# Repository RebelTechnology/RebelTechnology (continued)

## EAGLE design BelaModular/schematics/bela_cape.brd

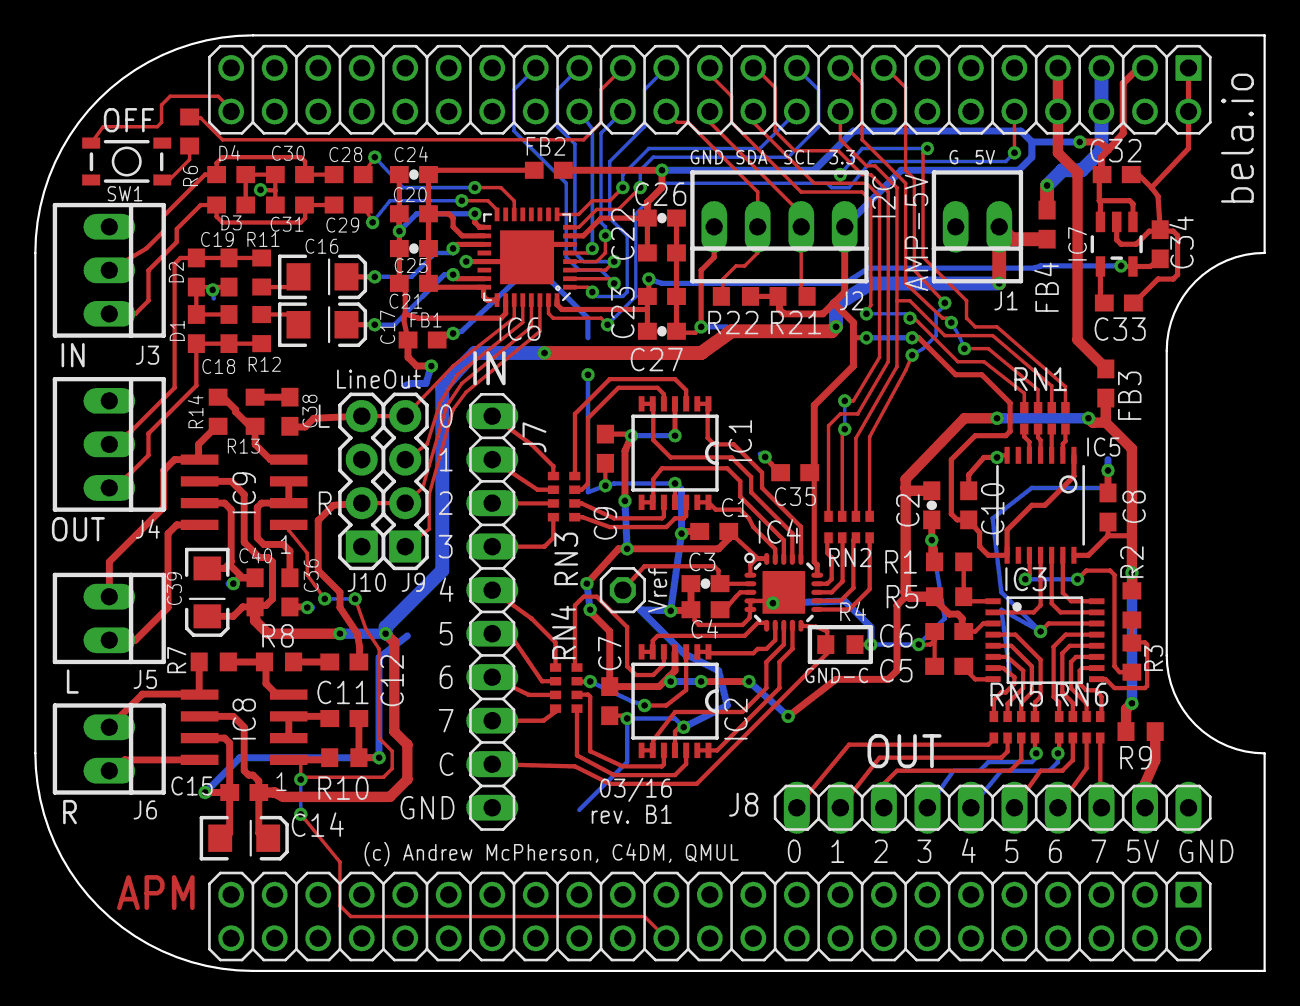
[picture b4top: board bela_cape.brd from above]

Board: 2 copper layers, 71.8 x 54.6 mm, 90 parts (0 on the bottom side), 114 nets.

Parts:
C1, C4, C5, C6, C7, C8, C9, C10, C11, C15, C35, C36, C40: 0.1uF; C0603
C2, C3: 10uF; 0603-CAP
C12, C38: 1uF; C0603
C14, C39: 47uF; EIA3216
C16, C17: 47uf; EIA3216
C18, C19, C30, C31: 47pF; C0603
C20, C21, C22, C23, C28, C29: 0.1uf; C0603
C24, C25, C26, C27: 10uf,10V; 0603-CAP
C32: 1uf; C0603
C33: .01uf; C0603
C34: 2.2uf; C0603
D1, D2, D3, D4: PGB0010603MR; 0603
FB1, FB2, FB3, FB4: FB; 0603
IC1, IC2: ADD8704RU; TSSOP14
IC3: AD5668; TSSOP16-PW
IC4: AD7699; LFCSP20-LEADS
IC5: TSSOP14
IC6: TLV320AIC3104; QFN-32
IC7: V_REG_LDOSMD; SOT23-5
IC8, IC9: LM4876; SO8
J1, J5, J6: 22-23-2021
J2: 22-23-2041
J3, J4: 22-23-2031
J7, J8: 1X10
J9, J10: 1X04
R1, R2, R4, R6: 0; R0603
R3, R5: DNI; R0603
R7, R8, R10, R13, R14: 22k; R0603
R9: 100; R0603
R11, R12: 33; R0603
R21, R22: 2.2k; R0603
RN1, RN2: 22; 0603-ARC
RN3, RN4, RN5, RN6: 220; 0603-ARC
S1: SWITCH-MOMENTARY-2SMD-5; TACTILE_SWITCH_SMD-4
TP1: 1X01
U$1: BEAGLEBONE_OUTLINE; BEAGLEBONE_SHIELD

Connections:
1.8V: C23.1, C27.2, C34.1, IC6.32, IC7.5
3.3V: C10.1, C22.1, C26.2, C32.1, C35.1, FB2.2, IC4.15, IC5.1, IC5.8, IC6.7, IC7.1, IC7.3, J2.1, R21.2, R22.2, U$1.49
+5V_ADC_DAC: C1.1, C2.1, C6.1, C7.1, C8.1, C9.1, FB3.1, IC1.4, IC2.4, IC3.3, IC4.1, IC4.20, IC5.14, R2.1, R5.1, R9.2
+5V_AMP: C14.A, C15.1, C39.A, C40.1, FB4.2, IC8.6, IC9.6, J1.1
+5V_POW: FB4.1, U$1.51, U$1.52
+5V_SYS: FB3.2, U$1.53, U$1.54
AGND: C11.2, C14.C, C15.2, C18.2, C19.2, C20.2, C21.2, C24.1, C25.1, C30.2, C31.1, C36.2, C39.C, C40.2, D1.1, D2.1, D3.1, D4.1, FB1.1, IC6.17, IC6.26, IC8.7, IC9.7, J3.1, J4.1, R10.2
AMP_SH/: IC8.1, IC9.1, R10.1, U$1.26
AUDIO_INL: C28.1, C30.1, D4.2, J3.2
AUDIO_INR: C29.2, C31.2, D3.2, J3.3
AUD_3V3: C20.1, C21.1, C24.2, C25.2, FB2.1, IC6.18, IC6.24, IC6.25
AUD_BCLK: IC6.2, U$1.77
AUD_DIN: IC6.5, U$1.76
AUD_DOUT: IC6.4, U$1.74
AUD_HPLOUT: C16.A, IC6.19
AUD_HPROUT: C17.A, IC6.23
AUD_MCLK: IC6.1, U$1.71
AUD_WCLK: IC6.3, U$1.75
DGND: C1.2, C2.2, C3.2, C4.2, C5.2, C6.2, C7.2, C8.2, C9.2, C10.2, C22.2, C23.2, C26.1, C27.1, C32.2, C33.2, C34.2, C35.2, FB1.2, IC1.11, IC2.11, IC3.14, IC4.4, IC4.5, IC4.EXP, IC5.7, IC6.6, IC6.21, IC6.EP, IC7.2, J1.2, J2.4, J7.10, J8.10, R1.2, R4.1, S1.4, U$1.1, U$1.2, U$1.47, U$1.48, U$1.89, U$1.90, U$1.91, U$1.92
HPL: C19.1, D2.2, J4.2, R11.1
HPR: C18.1, D1.2, J4.3, R12.1
I2C1_SCL: J2.2, R21.1, U$1.70
I2C1_SDA: J2.3, R22.1, U$1.72
LEFT_LOM: IC6.28, J9.3
LEFT_LOP: IC6.27, J9.4
LEFT_LOP_RETURN: C38.2, J10.4
LINE1LP: C28.2, IC6.14
LINE1RP: C29.1, IC6.16
unnamed: IC3.16, IC5.13
unnamed: IC3.15, IC5.12
unnamed: IC3.2, IC5.11
unnamed: IC3.9, R2.2, R3.2
unnamed: IC1.1, IC1.2, IC4.16
unnamed: IC1.6, IC1.7, IC4.17
unnamed: IC1.8, IC1.9, IC4.18
unnamed: IC1.13, IC1.14, IC4.19
unnamed: IC2.1, IC2.2, IC4.7
unnamed: IC2.6, IC2.7, IC4.6
unnamed: IC2.8, IC2.9, IC4.8
unnamed: IC2.13, IC2.14, IC4.9
unnamed: IC5.10, R3.1
unnamed: IC4.11, RN2.4
unnamed: C5.1, IC3.8
unnamed: IC5.2, RN1.8
unnamed: IC5.3, RN1.7
unnamed: IC5.4, RN1.6
unnamed: IC5.5, RN1.5
unnamed: IC4.12, RN2.3
unnamed: C3.1, IC4.2, TP1.1
unnamed: C4.1, IC4.3
unnamed: IC4.13, RN2.2
unnamed: IC4.14, RN2.1
unnamed: IC4.10, J7.9, R4.2
unnamed: IC9.4, R13.1, R14.2
unnamed: IC1.3, RN3.4
unnamed: IC8.4, R7.2, R8.1
unnamed: IC1.5, RN3.3
unnamed: IC1.10, RN3.2
unnamed: IC1.12, RN3.1
unnamed: IC2.5, RN4.4
unnamed: IC2.3, RN4.3
unnamed: IC2.10, RN4.2
unnamed: IC2.12, RN4.1
unnamed: IC3.1, R1.1, R5.2
unnamed: J7.1, RN3.5
unnamed: J7.2, RN3.6
unnamed: J7.3, RN3.7
unnamed: J7.4, RN3.8
unnamed: J7.5, RN4.5
unnamed: J7.6, RN4.6
unnamed: J7.7, RN4.7
unnamed: J7.8, RN4.8
unnamed: IC3.7, RN5.4
unnamed: IC3.6, RN5.3
unnamed: IC3.5, RN5.2
unnamed: IC3.4, RN5.1
unnamed: IC3.13, RN6.4
unnamed: IC3.12, RN6.3
unnamed: IC3.11, RN6.2
unnamed: J8.8, RN6.8
unnamed: C11.1, IC8.2, IC8.3
unnamed: C16.C, R11.2
unnamed: C12.2, R8.2
unnamed: IC8.5, J6.1, R7.1
unnamed: R6.1, S1.1
unnamed: C17.C, R12.2
unnamed: C36.1, IC9.2, IC9.3
unnamed: J8.9, R9.1
unnamed: C33.1, IC7.4
unnamed: C38.1, R13.2
unnamed: IC9.5, J5.1, R14.1
unnamed: IC9.8, J5.2
unnamed: IC8.8, J6.2
unnamed: IC3.10, RN6.1
unnamed: J8.7, RN6.7
unnamed: J8.6, RN6.6
unnamed: J8.5, RN6.5
unnamed: J8.4, RN5.8
unnamed: J8.3, RN5.7
unnamed: J8.2, RN5.6
unnamed: J8.1, RN5.5
RESETN: IC6.31, U$1.56
RIGHT_LOP: IC6.29, J9.2
RIGHT_LOP_RETURN: C12.1, J10.2
RIGHT_ROM: IC6.30, J9.1
SCL: IC6.8, U$1.65
SDA: IC6.9, U$1.66
SHUTDOWN_REQ/: R6.2, U$1.73
SPI_ADC_CNV: RN2.5, U$1.61
SPI_DAC_CLR/: RN1.4, U$1.69
SPI_DAC_SYNC/: RN1.3, U$1.63
SPI_MISO: RN2.8, U$1.67
SPI_MOSI: RN1.2, RN2.6, U$1.64
SPI_SCK: RN1.1, RN2.7, U$1.68

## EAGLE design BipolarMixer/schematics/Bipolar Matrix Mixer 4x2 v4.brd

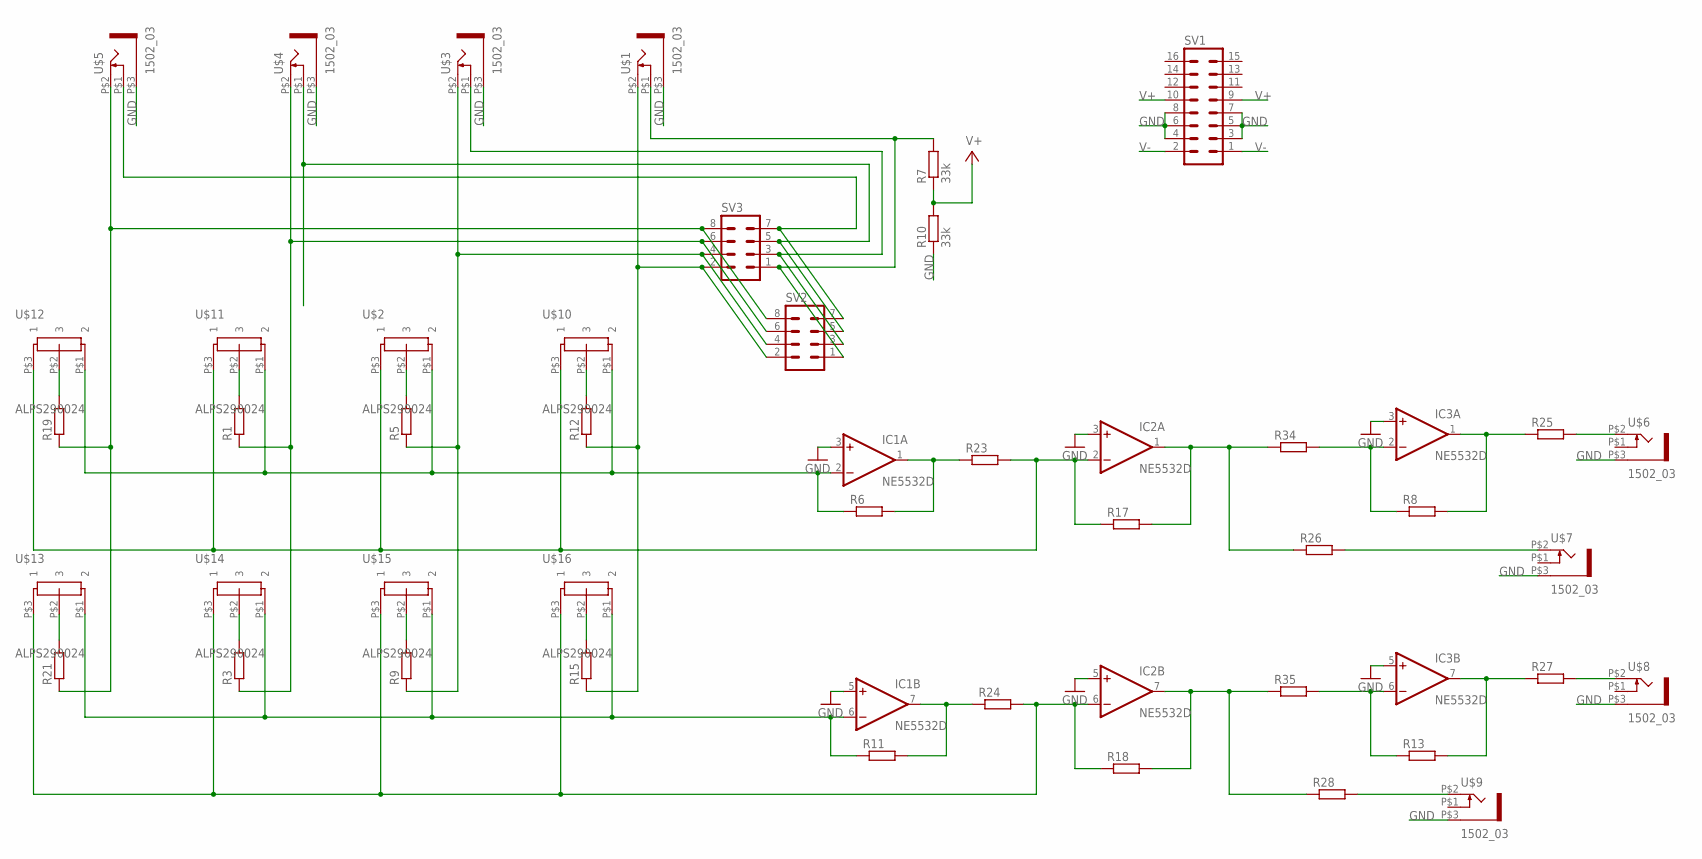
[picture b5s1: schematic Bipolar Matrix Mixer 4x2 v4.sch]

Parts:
IC1, IC2, IC3: NE5532D; SO08
R1, R3, R5, R6, R8, R9, R11, R12, R13, R15, R17, R18, R19, R21, R23, R24, R25, R26, R27, R28, R34, R35: R-EU_R0603; R0603
R7, R10: 33k; R0603
SV1: MA08-2
SV2, SV3: MA04-2
U$1, U$3, U$4, U$5, U$6, U$7, U$8, U$9: 1502_03
U$2, U$10, U$11, U$12, U$13, U$14, U$15, U$16: ALPS290024; POT

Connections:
GND: IC1.3 (+IN), IC1.5 (+IN), IC2.3 (+IN), IC2.5 (+IN), IC3.3 (+IN), IC3.5 (+IN), R10.1, SV1.3, SV1.4, SV1.5, SV1.6, SV1.7, SV1.8, U$1.P$3 (5), U$3.P$3 (5), U$4.P$3 (5), U$5.P$3 (5), U$6.P$3 (5), U$7.P$3 (5), U$8.P$3 (5), U$9.P$3 (5)
unnamed: IC2.1 (OUT), R17.2, R26.1, R34.1
unnamed: R1.1, R3.1, SV2.6, SV3.6, U$4.P$2 (3)
unnamed: IC1.7 (OUT), R11.2, R24.1
unnamed: IC1.1 (OUT), R6.2, R23.1
unnamed: IC3.7 (OUT), R13.2, R27.1
unnamed: IC3.1 (OUT), R8.2, R25.1
unnamed: R19.2, U$12.P$2 (3)
unnamed: R21.2, U$13.P$2 (3)
unnamed: R25.2, U$6.P$2 (3)
unnamed: R26.2, U$7.P$2 (3)
unnamed: R1.2, U$11.P$2 (3)
unnamed: R3.2, U$14.P$2 (3)
unnamed: IC2.7 (OUT), R18.2, R28.1, R35.1
unnamed: R27.2, U$8.P$2 (3)
unnamed: IC2.2 (-IN), R17.1, R23.2, U$2.P$3 (1), U$10.P$3 (1), U$11.P$3 (1), U$12.P$3 (1)
unnamed: R28.2, U$9.P$2 (3)
unnamed: IC3.2 (-IN), R8.1, R34.2
unnamed: R5.1, R9.1, SV2.4, SV3.4, U$3.P$2 (3)
unnamed: SV2.3, SV3.3, U$3.P$1 (4)
unnamed: R5.2, U$2.P$2 (3)
unnamed: R9.2, U$15.P$2 (3)
unnamed: IC3.6 (-IN), R13.1, R35.2
unnamed: IC1.2 (-IN), R6.1, U$2.P$1 (2), U$10.P$1 (2), U$11.P$1 (2), U$12.P$1 (2)
unnamed: R12.1, R15.1, SV2.2, SV3.2, U$1.P$2 (3)
unnamed: R19.1, R21.1, SV2.8, SV3.8, U$5.P$2 (3)
unnamed: IC2.6 (-IN), R18.1, R24.2, U$13.P$3 (1), U$14.P$3 (1), U$15.P$3 (1), U$16.P$3 (1)
unnamed: IC1.6 (-IN), R11.1, U$13.P$1 (2), U$14.P$1 (2), U$15.P$1 (2), U$16.P$1 (2)
unnamed: R7.2, SV2.1, SV3.1, U$1.P$1 (4)
unnamed: SV2.5, SV3.5, U$4.P$1 (4)
unnamed: SV2.7, SV3.7, U$5.P$1 (4)
unnamed: R12.2, U$10.P$2 (3)
unnamed: R15.2, U$16.P$2 (3)
V+: IC1.8 (V+), IC2.8 (V+), IC3.8 (V+), R7.1, R10.2, SV1.9, SV1.10
V-: IC1.4 (V-), IC2.4 (V-), IC3.4 (V-), SV1.1, SV1.2

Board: 2 copper layers, 46 parts (0 on the bottom side), 35 nets, no tracks yet.

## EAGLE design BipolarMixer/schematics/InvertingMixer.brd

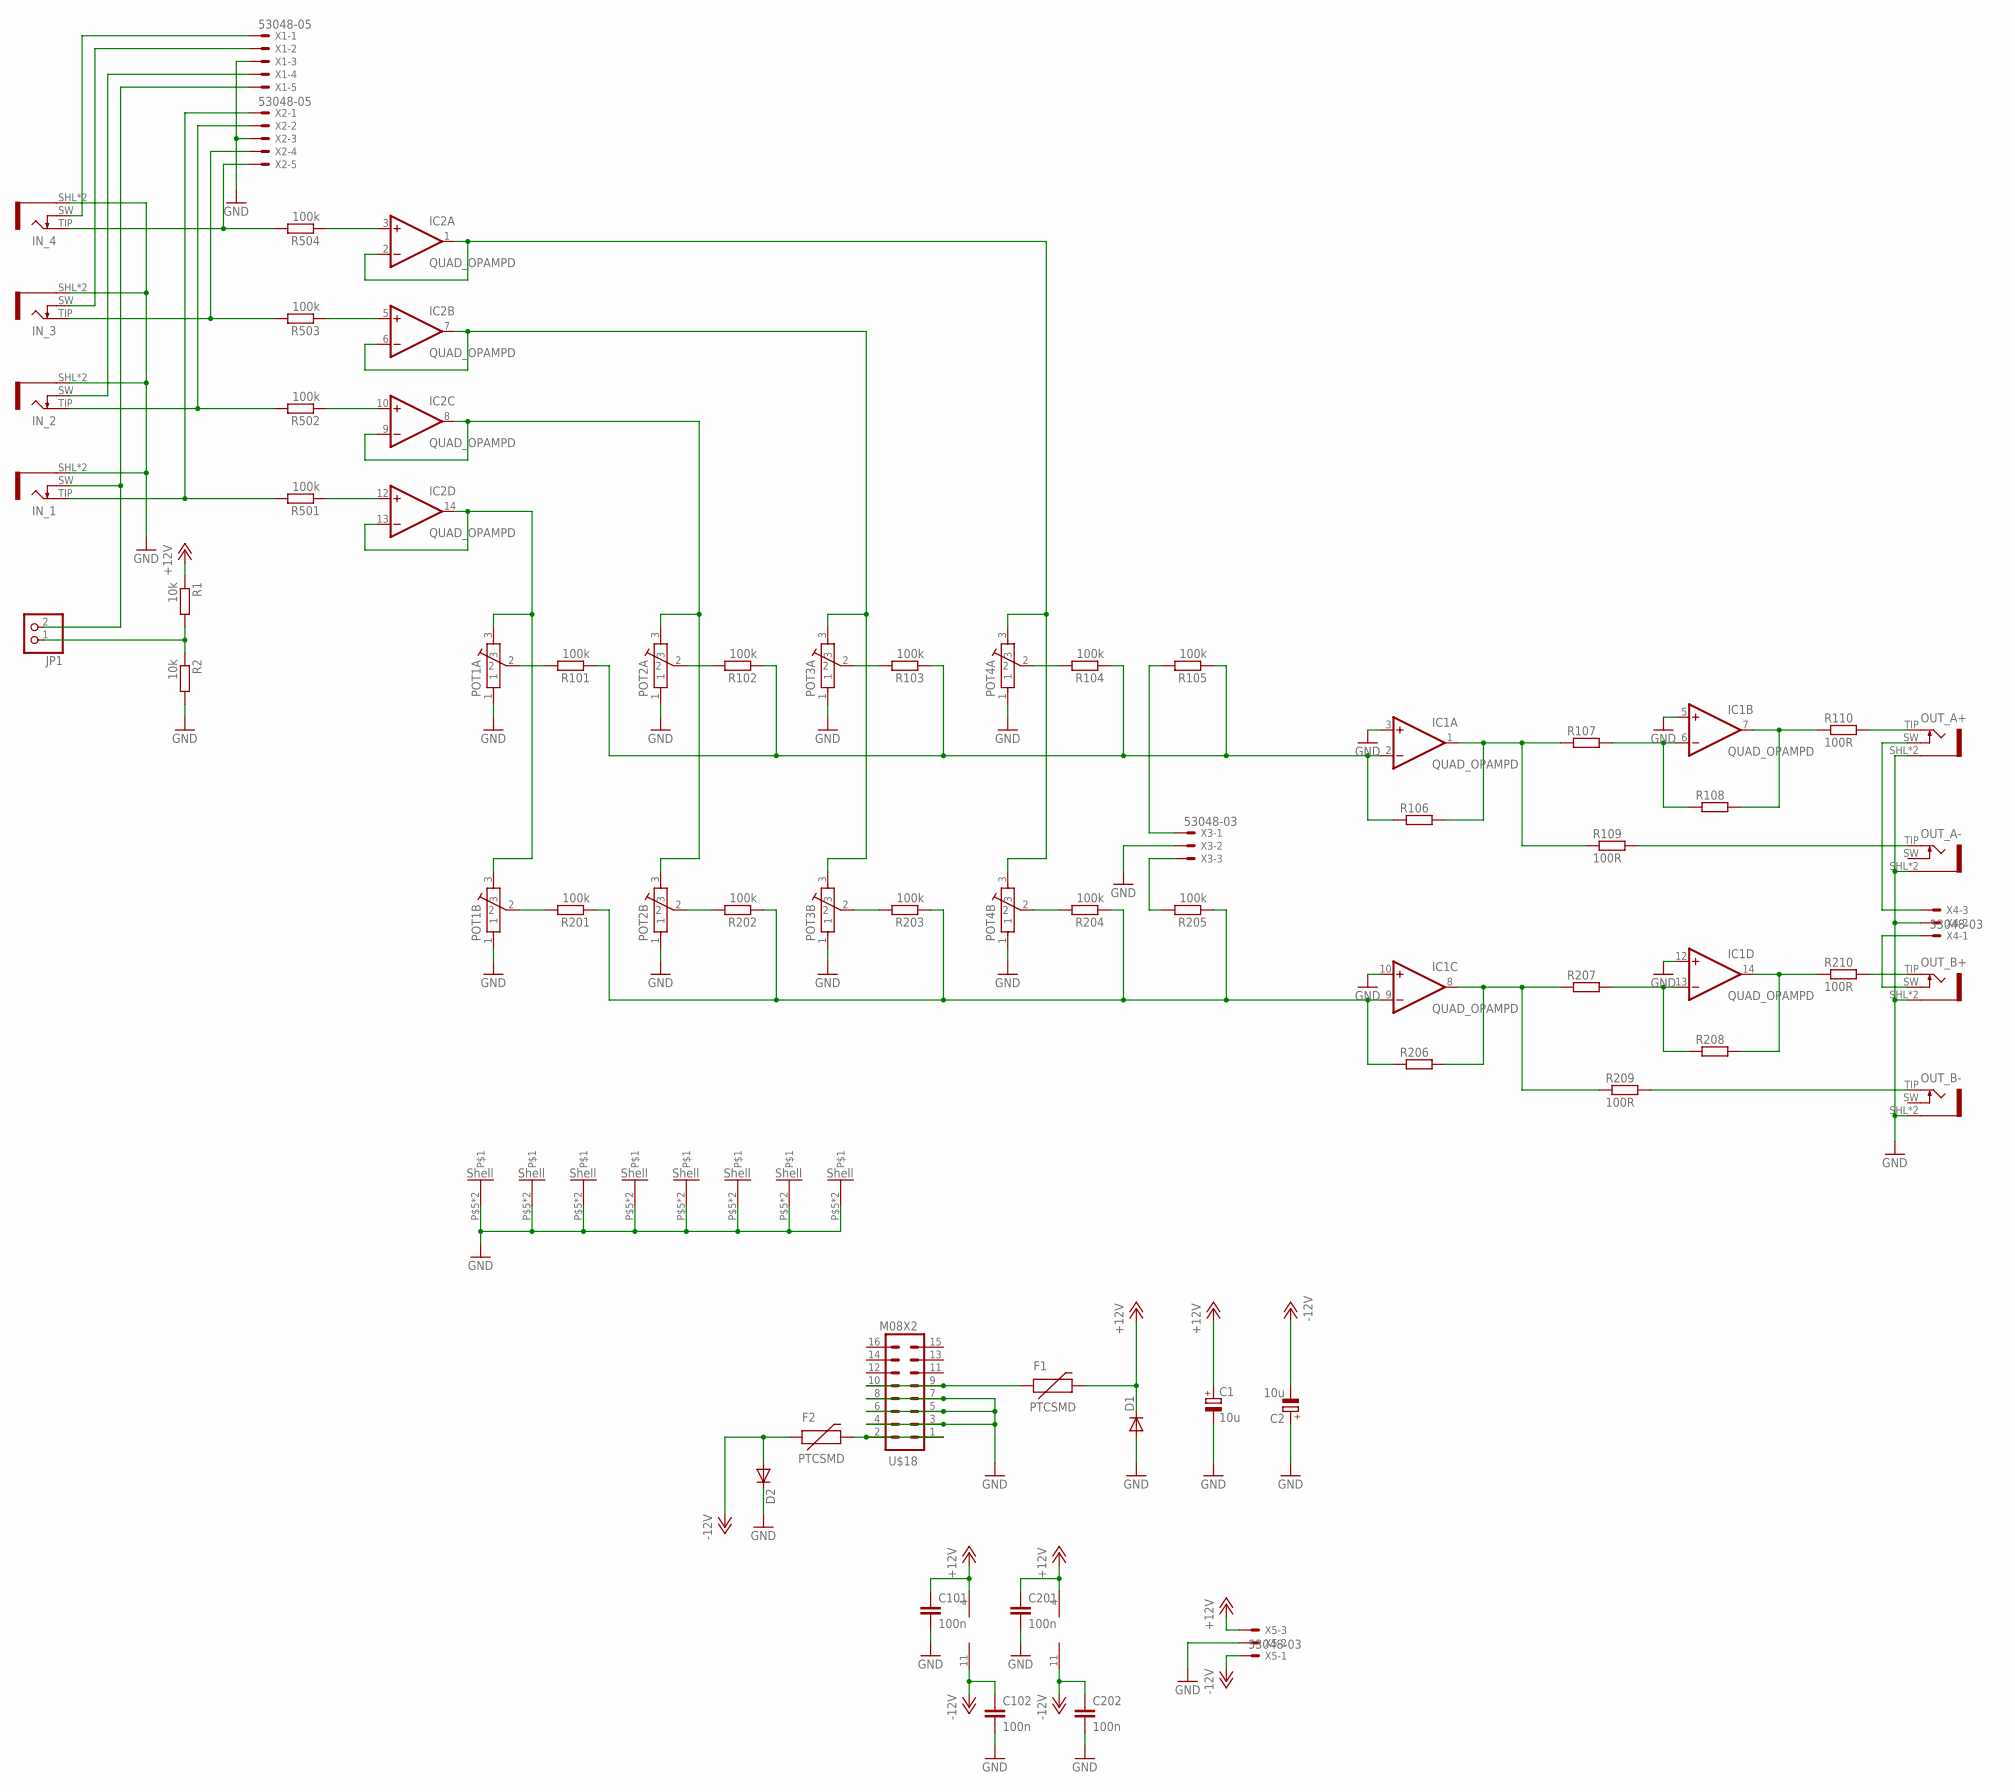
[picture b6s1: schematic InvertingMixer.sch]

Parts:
C1, C2: 10u; PANASONIC_A
C101, C102, C201, C202: 100n; C0603
D1, D2: DIODESMA; SMA-DIODE
F1, F2: PTCSMD; PTC-1206
IC1, IC2: QUAD_OPAMPD; SO14
IN_1, IN_2, IN_3, IN_4: JACK-PJ-301B; PJ-301B
JP1: PINHD-1X2; 1X02
OUT_A+: JACK-PJ-301B; PJ-301B
OUT_A-: JACK-PJ-301B; PJ-301B
OUT_B+: JACK-PJ-301B; PJ-301B
OUT_B-: JACK-PJ-301B; PJ-301B
POT1A, POT1B, POT2A, POT2B, POT3A, POT3B, POT4A, POT4B: POT-ALPS-RK09L1140
R1, R2: 10k; R0603
R101, R102, R103, R104, R105, R201, R202, R203, R204, R205, R501, R502, R503, R504: 100k; R0603
R106, R107, R108, R206, R207, R208: R-EU_R0603; R0603
R109, R110, R209, R210: 100R; R0603
U$18: M08X2; 2X8
X1, X2: 53048-05
X3, X4, X5: 53048-03

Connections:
+12V: C1.+, C101.1, C201.1, D1.C, F1.2, IC1.4 (V+), IC2.4 (V+), R1.1, X5.3
-12V: C2.-, C102.1, C202.1, D2.A, F2.1, IC1.11 (V-), IC2.11 (V-), X5.1
GND: C1.-, C2.+, C101.2, C102.2, C201.2, C202.2, D1.A, D2.C, IC1.3 (+IN), IC1.5 (+IN), IC1.10 (+IN), IC1.12 (+IN), IN_1.SHL (SLEEVE), IN_1.SLV (SLEEVE), IN_2.SHL (SLEEVE), IN_2.SLV (SLEEVE), IN_3.SHL (SLEEVE), IN_3.SLV (SLEEVE), IN_4.SHL (SLEEVE), IN_4.SLV (SLEEVE), OUT_A+.SHL (SLEEVE), OUT_A+.SLV (SLEEVE), OUT_A-.SHL (SLEEVE), OUT_A-.SLV (SLEEVE), OUT_B+.SHL (SLEEVE), OUT_B+.SLV (SLEEVE), OUT_B-.SHL (SLEEVE), OUT_B-.SLV (SLEEVE), POT1A.1, POT1A.P$5, POT1A.P$6, POT1B.1, POT1B.P$5, POT1B.P$6, POT2A.1, POT2A.P$5, POT2A.P$6, POT2B.1, POT2B.P$5, POT2B.P$6, POT3A.1, POT3A.P$5, POT3A.P$6, POT3B.1, POT3B.P$5, POT3B.P$6, POT4A.1, POT4A.P$5, POT4A.P$6, POT4B.1, POT4B.P$5, POT4B.P$6, R2.2, U$18.3, U$18.4, U$18.5, U$18.6, U$18.7, U$18.8, X1.3, X2.3, X3.2, X4.2, X5.2
unnamed: IC1.1 (OUT), R106.2, R107.1, R109.1
unnamed: R205.2, X3.3
unnamed: OUT_A+.SW, X4.3
unnamed: OUT_B+.SW, X4.1
unnamed: IC1.14 (OUT), R208.2, R210.1
unnamed: IC1.7 (OUT), R108.2, R110.1
unnamed: JP1.1, R1.2, R2.1
unnamed: OUT_A+.TIP, R110.2
unnamed: OUT_A-.TIP, R109.2
unnamed: IC1.8 (OUT), R206.2, R207.1, R209.1
unnamed: OUT_B+.TIP, R210.2
unnamed: OUT_B-.TIP, R209.2
unnamed: IC1.6 (-IN), R107.2, R108.1
unnamed: POT1B.2, R201.2
unnamed: IC1.13 (-IN), R207.2, R208.1
unnamed: IC2.8 (OUT), IC2.9 (-IN), POT2A.3, POT2B.3
unnamed: POT1A.2, R101.2
unnamed: POT2B.2, R202.2
unnamed: POT3B.2, R203.2
unnamed: IN_1.TIP, R501.2, X2.1
unnamed: IC2.13 (-IN), IC2.14 (OUT), POT1A.3, POT1B.3
unnamed: IN_4.TIP, R504.2, X2.5
unnamed: IN_3.TIP, R503.2, X2.4
unnamed: IN_2.TIP, R502.2, X2.2
unnamed: IN_4.SW, X1.1
unnamed: IN_3.SW, X1.2
unnamed: IN_2.SW, X1.4
unnamed: IN_1.SW, JP1.2, X1.5
unnamed: IC2.3 (+IN), R504.1
unnamed: IC2.5 (+IN), R503.1
unnamed: POT4B.2, R204.2
unnamed: POT4A.2, R104.2
unnamed: IC2.10 (+IN), R502.1
unnamed: POT3A.2, R103.2
unnamed: IC2.12 (+IN), R501.1
unnamed: POT2A.2, R102.2
unnamed: IC1.2 (-IN), R101.1, R102.1, R103.1, R104.1, R105.1, R106.1
unnamed: IC2.6 (-IN), IC2.7 (OUT), POT3A.3, POT3B.3
unnamed: F1.1, U$18.9, U$18.10
unnamed: F2.2, U$18.1, U$18.2
unnamed: IC2.1 (OUT), IC2.2 (-IN), POT4A.3, POT4B.3
unnamed: IC1.9 (-IN), R201.1, R202.1, R203.1, R204.1, R205.1, R206.1
unnamed: R105.2, X3.1

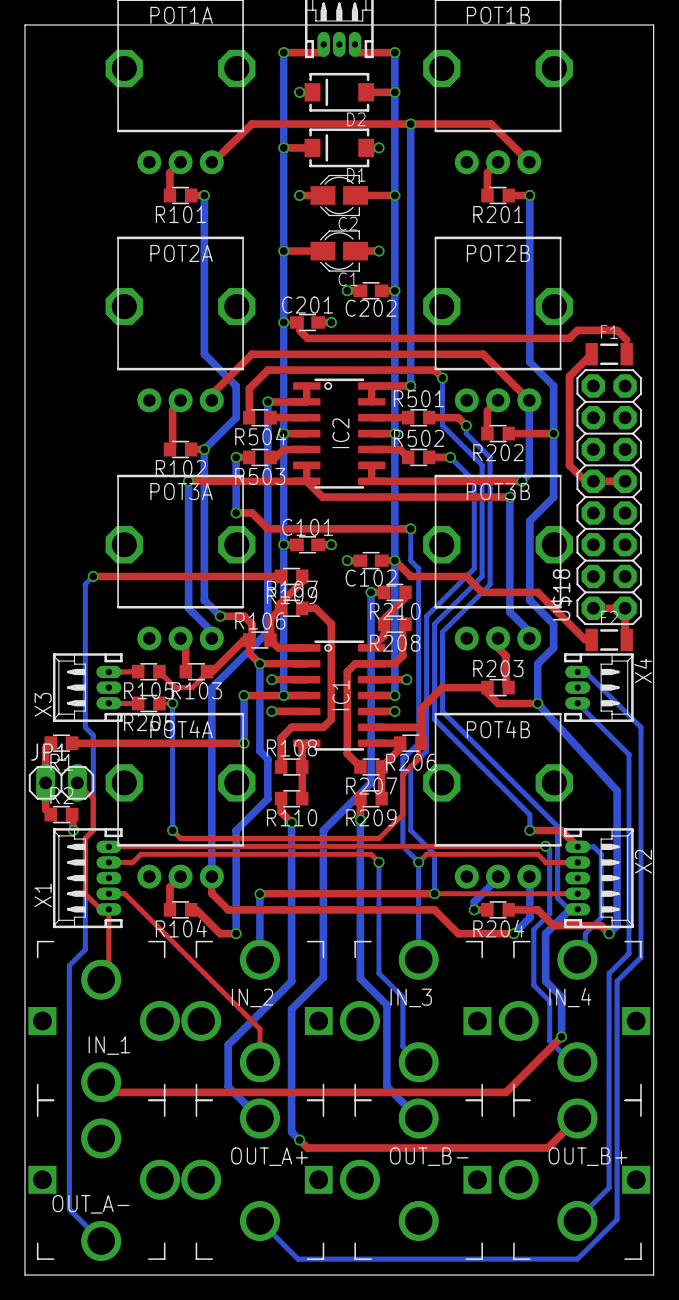
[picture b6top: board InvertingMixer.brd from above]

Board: 2 copper layers, 50.3 x 100.0 mm, 61 parts (0 on the bottom side), 46 nets.

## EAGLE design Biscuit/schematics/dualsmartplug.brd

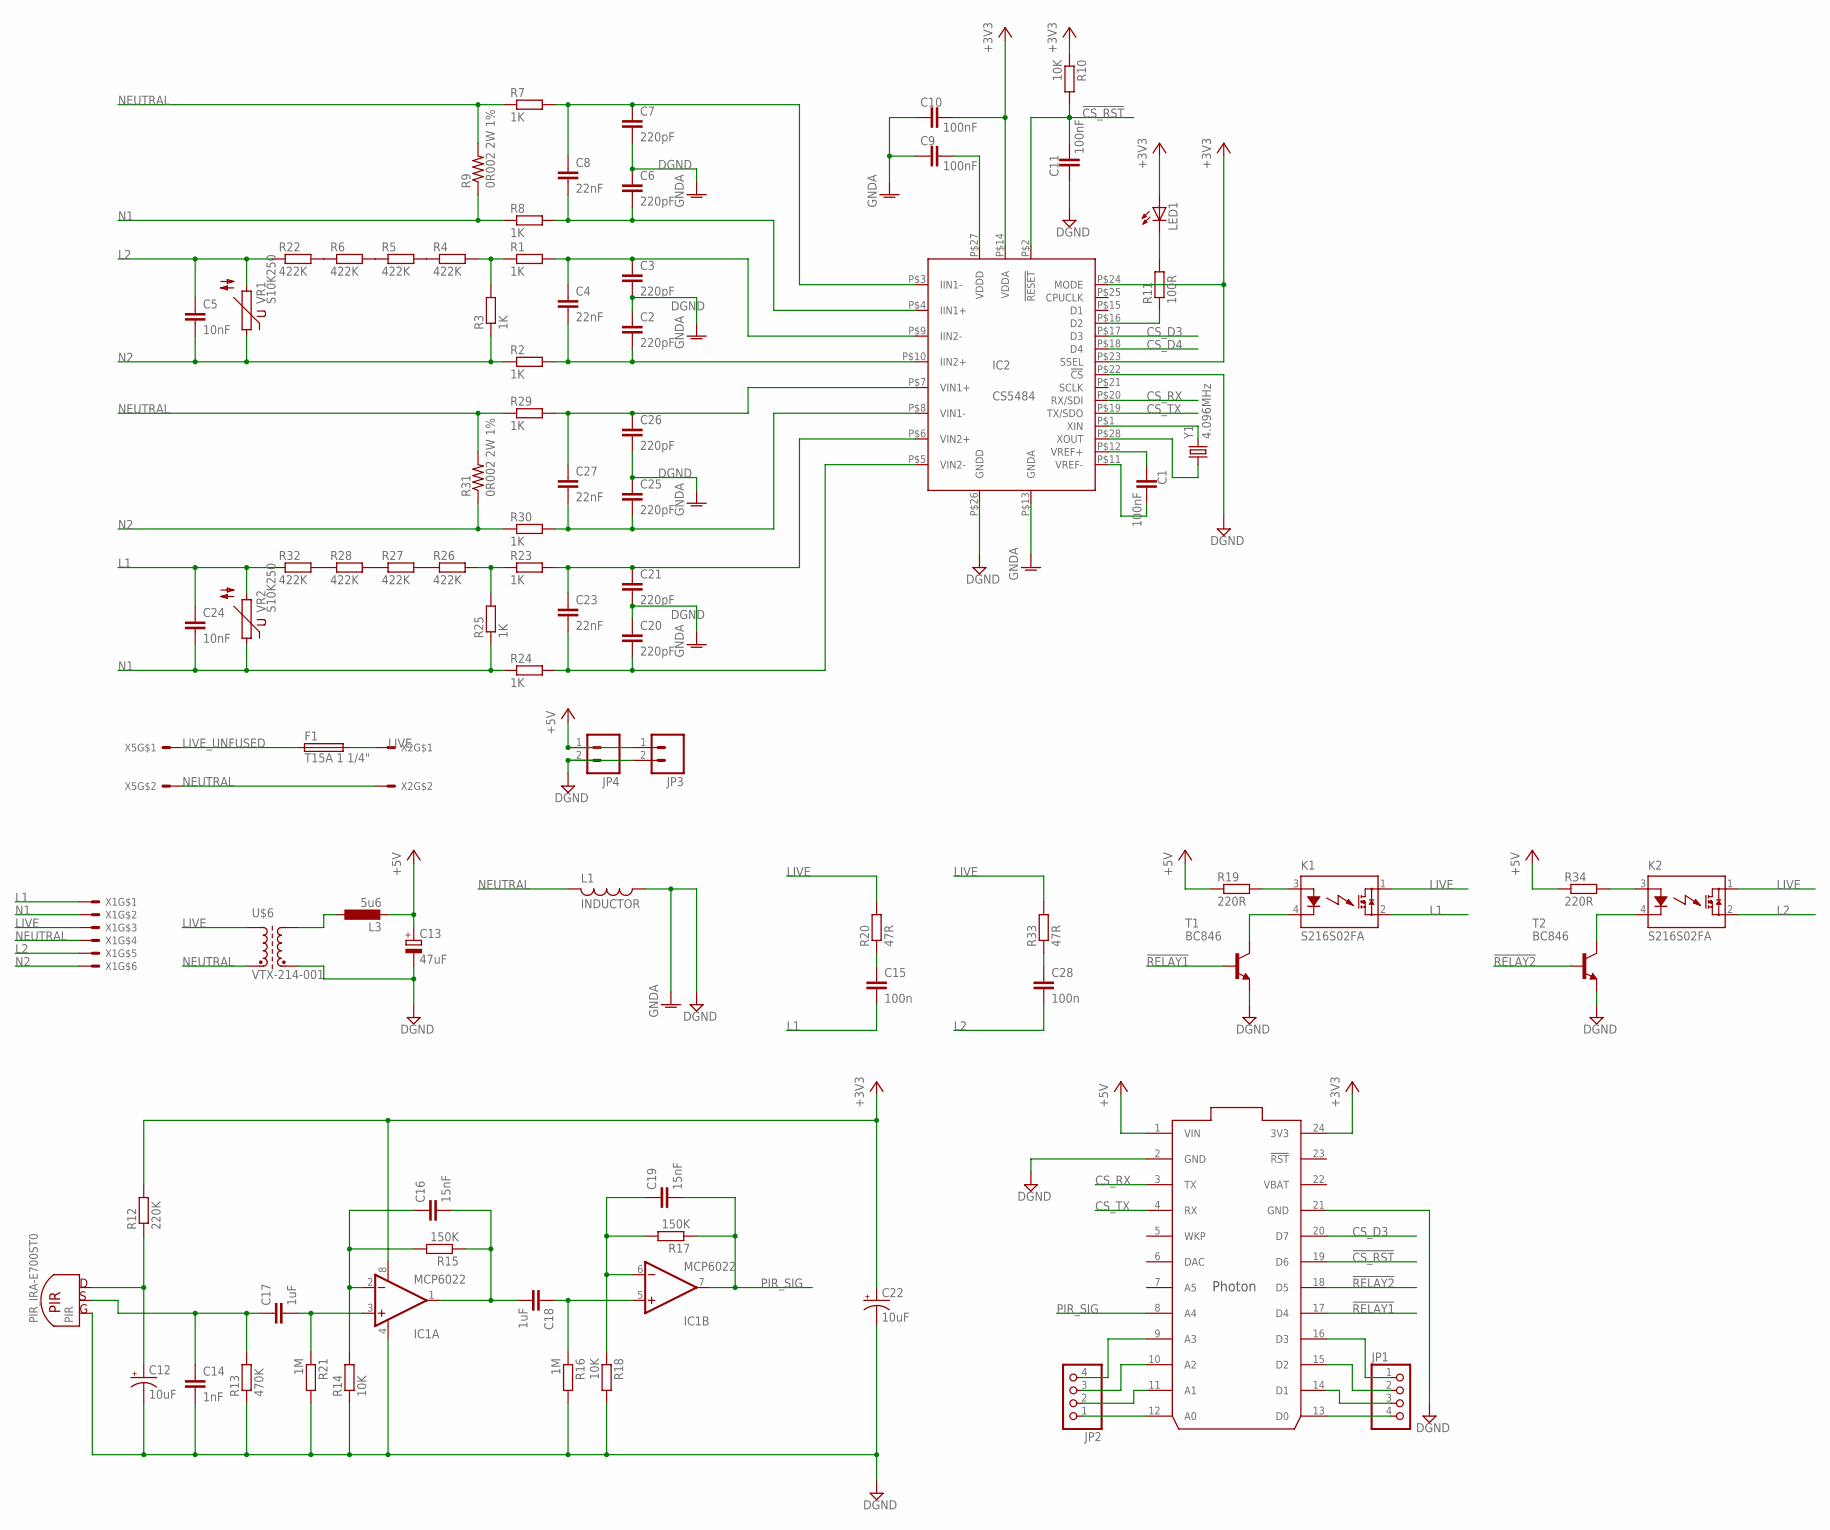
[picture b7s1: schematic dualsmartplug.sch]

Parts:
C1, C9, C10, C11: 100nF; 0603-CAP
C2, C3, C6, C7, C20, C21, C25, C26: 220pF; 0603-CAP
C4, C8, C23, C27: 22nF; 0603-CAP
C5, C24: 10nF; 0603-CAP
C12, C22: 10uF; EIA3216
C13: 47uF; 153CLV-0505
C14: 1nF; 0603-CAP
C15, C28: 100n; C150-054X183
C16, C19: 15nF; 0603-CAP
C17, C18: 1uF; 0603-CAP
F1: T15A 1 1/4"; SHURTER
IC1: MCP6022; SO08
IC2: CS5484; QFN28-5X5
JP1, JP2: PINHD-1X4; 1X04
JP3, JP4: M02PTH; 1X02
K1, K2: S216S02FA; S216S02F
L1: INDUCTOR; 0603
L3: 5u6; ELLCTP
LED1: LEDCHIPLED_1206; CHIPLED_1206
PIR: PIR_IRA-E700ST0
R1, R2, R3, R7, R8, R23, R24, R25, R29, R30: 1K; 0603
R4, R5, R6, R22, R26, R27, R28, R32: 422K; 0603
R9, R31: 0R002 2W 1%; R2512
R10, R14, R18: 10K; 0603
R11: 100R; 0603
R12: 220K; 0603
R13: 470K; 0603
R15, R17: 150K; 0603
R16, R21: 1M; 0603
R19, R34: 220R; 0603
R20, R33: 47R; 0617V
T1, T2: BC846; SOT23
U$2: PHOTON_WITH_HEADERS; PHOTON
U$6: VTX-214-001
VR1, VR2: S10K250
X1: MOLEX-39357-6
X2, X5: MOLEX-39357-2; MOLEX-39357
Y1: 4.096MHz; CRYSTAL-SMD-10.5X4.8-2PIN

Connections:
!CS_RST: C11.2, IC2.P$2 (!RESET), R10.2, U$2.19 (D6)
!RELAY1: T1.1 (B), U$2.17 (D4)
!RELAY2: T2.1 (B), U$2.18 (D5)
+3V3: C10.2, C22.A (+), IC1.8 (V+), IC2.P$14 (VDDA), IC2.P$23 (SSEL), IC2.P$24 (MODE), LED1.A, R10.1, R12.2, U$2.24 (3V3)
+5V: C13.+, JP3.1, JP4.1, L3.2, R19.1, R34.1, U$2.1 (VIN)
CS_D3: IC2.P$17 (D3), U$2.20 (D7)
CS_D4: IC2.P$18 (D4)
CS_RX: IC2.P$20 (RX/SDI), U$2.3 (TX)
CS_TX: IC2.P$19 (TX/SDO), U$2.4 (RX)
DGND: C2.1, C3.2, C6.1, C7.2, C9.1, C10.1, C11.1, C12.C (-), C13.-, C14.2, C20.1, C21.2, C22.C (-), C25.1, C26.2, IC1.4 (V-), IC2.P$13 (GNDA), IC2.P$22 (!CS), IC2.P$26 (GNDD), JP3.2, JP4.2, L1.1, PIR.GND, R13.1, R14.1, R16.2, R18.2, R21.2, T1.2 (E), T2.2 (E), U$2.2 (GND), U$2.21 (GND), U$6.P$V- (E2)
L1: C15.2, C24.1, K1.2 (DS2), R32.1, VR2.2, X1.P$1
L2: C5.1, C28.2, K2.2 (DS2), R22.1, VR1.2, X1.P$5
LIVE: F1.P$7 (2A), K1.1 (DS1), K2.1 (DS1), R20.2, R33.2, U$6.P$L (A1), X1.P$3, X2.P$1
LIVE_UNFUSED: F1.P$5 (1A), X5.P$1
N1: C24.2, R8.1, R9.1, R24.1, R25.1, VR2.1, X1.P$2
N2: C5.2, R2.1, R3.1, R30.1, R31.1, VR1.1, X1.P$6
unnamed: IC2.P$1 (XIN), Y1.P$2 (2)
unnamed: IC2.P$28 (XOUT), Y1.P$1 (1)
unnamed: C1.1, IC2.P$12 (VREF+)
unnamed: C1.2, IC2.P$11 (VREF-)
unnamed: C9.2, IC2.P$27 (VDDD)
unnamed: C12.A (+), PIR.DRAIN+ (DRAIN), R12.1
unnamed: C2.2, C4.2, IC2.P$10 (IIN2+), R2.2
unnamed: C3.1, C4.1, IC2.P$9 (IIN2-), R1.2
unnamed: C6.2, C8.2, IC2.P$4 (IIN1+), R8.2
unnamed: C7.1, C8.1, IC2.P$3 (IIN1-), R7.2
unnamed: R1.1, R3.2, R4.2
unnamed: C14.1, C17.1, PIR.SOURCE, R13.2
unnamed: R4.1, R5.2
unnamed: R5.1, R6.2
unnamed: C16.1, IC1.2 (-IN), R14.2, R15.2
unnamed: IC2.P$16 (D2), R11.1
unnamed: K1.4 (K), T1.3 (C)
unnamed: C17.2, IC1.3 (+IN), R21.1
unnamed: LED1.C, R11.2
unnamed: C18.1, IC1.5 (+IN), R16.1
unnamed: L3.1, U$6.P$V+ (A2)
unnamed: K1.3 (A), R19.2
unnamed: C15.1, R20.1
unnamed: C19.1, IC1.6 (-IN), R17.2, R18.1
unnamed: C16.2, C18.2, IC1.1 (OUT), R15.1
unnamed: JP2.1, U$2.12 (A0)
unnamed: JP2.2, U$2.11 (A1)
unnamed: JP2.3, U$2.10 (A2)
unnamed: JP2.4, U$2.9 (A3)
unnamed: JP1.4, U$2.13 (D0)
unnamed: JP1.3, U$2.14 (D1)
unnamed: JP1.2, U$2.15 (D2)
unnamed: JP1.1, U$2.16 (D3)
unnamed: R6.1, R22.2
unnamed: C20.2, C23.2, IC2.P$5 (VIN2-), R24.2
unnamed: C21.1, C23.1, IC2.P$6 (VIN2+), R23.2
unnamed: R23.1, R25.2, R26.2
unnamed: R26.1, R27.2
unnamed: R27.1, R28.2
unnamed: C25.2, C27.2, IC2.P$8 (VIN1-), R30.2
unnamed: C26.1, C27.1, IC2.P$7 (VIN1+), R29.2
unnamed: C28.1, R33.1
unnamed: R28.1, R32.2
unnamed: K2.4 (K), T2.3 (C)
unnamed: K2.3 (A), R34.2
NEUTRAL: L1.2, R7.1, R9.2, R29.1, R31.2, U$6.P$N (E1), X1.P$4, X2.P$2, X5.P$2
PIR_SIG: C19.2, IC1.7 (OUT), R17.1, U$2.8 (A4)
VBAT: U$2.22 (VBAT)

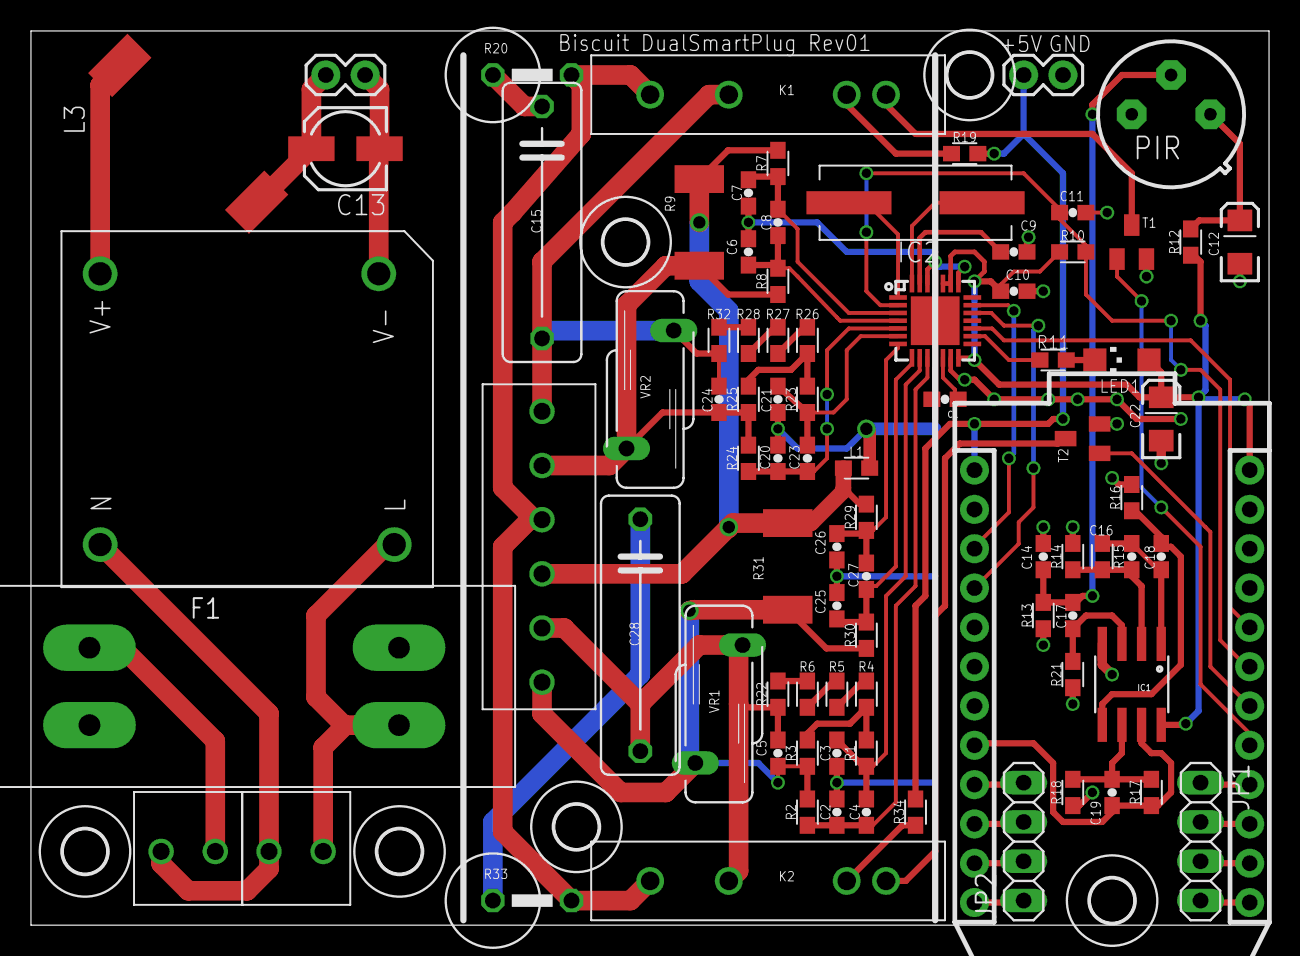
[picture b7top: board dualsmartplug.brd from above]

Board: 2 copper layers, 80.0 x 57.8 mm, 91 parts (0 on the bottom side), 62 nets.

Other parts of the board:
U$1, U$4, U$5, U$7, U$8, U$10: 2,8
